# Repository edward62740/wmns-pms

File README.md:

# Particulate Matter Sensor

This sensor measures particulate matter in the air, shows readings on a display and posts the data to InfluxDB. Extention of [WMNS](https://github.com/edward62740/Wireless-Mesh-Network-System).

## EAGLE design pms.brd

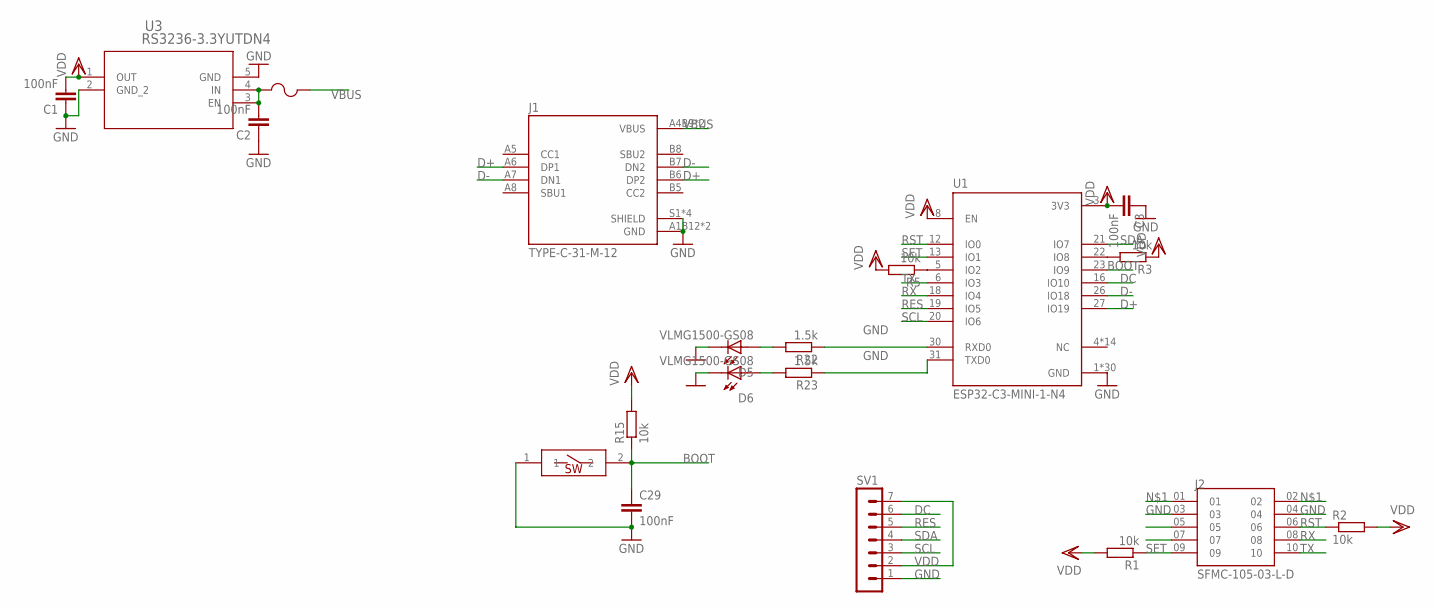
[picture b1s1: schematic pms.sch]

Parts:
C1, C2, C3, C29: 100nF; C0402
D5, D6: VLMG1500-GS08; LEDC1005X35N
F2: 1210L050YR1210LSERIES_LTF-L; 1210LSERIES_LTF-L
J1: TYPE-C-31-M-12; HRO_TYPE-C-31-M-12
J2: SFMC-105-03-L-D; SAMTEC_SFMC-105-03-L-D
R1, R2, R3, R5, R15: 10k; R0402
R22, R23: 1.5k; R0402
RESET: SMDSWITCH; RESC4217X170
SV1: MA07-1
U1: ESP32-C3-MINI-1-N4; XCVR_ESP32-C3-MINI-1-N4
U3: RS3236-3.3YUTDN4; UTDFN-1X1-4_JRT

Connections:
BOOT: C29.1, R15.1, RESET.2, U1.23 (IO9)
D+: J1.A6 (DP1), J1.B6 (DP2), U1.27 (IO19)
D-: J1.A7 (DN1), J1.B7 (DN2), U1.26 (IO18)
DC: SV1.6, U1.16 (IO10)
GND: C1.1, C2.1, C3.1, C29.2, D5.2, D6.2, J1.A1B12 (GND), J1.B1A12 (GND), J1.S1 (SHIELD), J1.S2 (SHIELD), J1.S3 (SHIELD), J1.S4 (SHIELD), J2.03, J2.04, RESET.1, SV1.1, U1.1 (GND), U1.2 (GND), U1.11 (GND), U1.14 (GND), U1.36 (GND), U1.37 (GND), U1.38 (GND), U1.39 (GND), U1.40 (GND), U1.41 (GND), U1.42 (GND), U1.43 (GND), U1.44 (GND), U1.45 (GND), U1.46 (GND), U1.47 (GND), U1.48 (GND), U1.49_1 (GND), U1.49_2 (GND), U1.49_3 (GND), U1.49_4 (GND), U1.49_5 (GND), U1.49_6 (GND), U1.49_7 (GND), U1.49_8 (GND), U1.49_9 (GND), U1.50 (GND), U1.51 (GND), U1.52 (GND), U1.53 (GND), U3.2 (GND_2), U3.5 (GND)
unnamed: C2.2, F2.2, J2.01, J2.02, U3.3 (EN), U3.4 (IN)
unnamed: R3.2, U1.22 (IO8)
unnamed: R5.1, U1.5 (IO2)
unnamed: R23.1, U1.31 (TXD0)
unnamed: R22.1, U1.30 (RXD0)
unnamed: D5.1, R22.2
unnamed: D6.1, R23.2
RES: SV1.5, U1.19 (IO5)
RST: J2.06, R2.1, U1.12 (IO0)
RX: J2.08, U1.18 (IO4)
SCL: SV1.3, U1.20 (IO6)
SDA: SV1.4, U1.21 (IO7)
SET: J2.09, R1.1, U1.13 (IO1)
TX: J2.10, U1.6 (IO3)
VBUS: F2.1, J1.A4B9 (VBUS), J1.B4A9 (VBUS)
VDD: C1.2, C3.2, R1.2, R2.2, R3.1, R5.2, R15.2, SV1.2, SV1.7, U1.3 (3V3), U1.8 (EN), U3.1 (OUT)

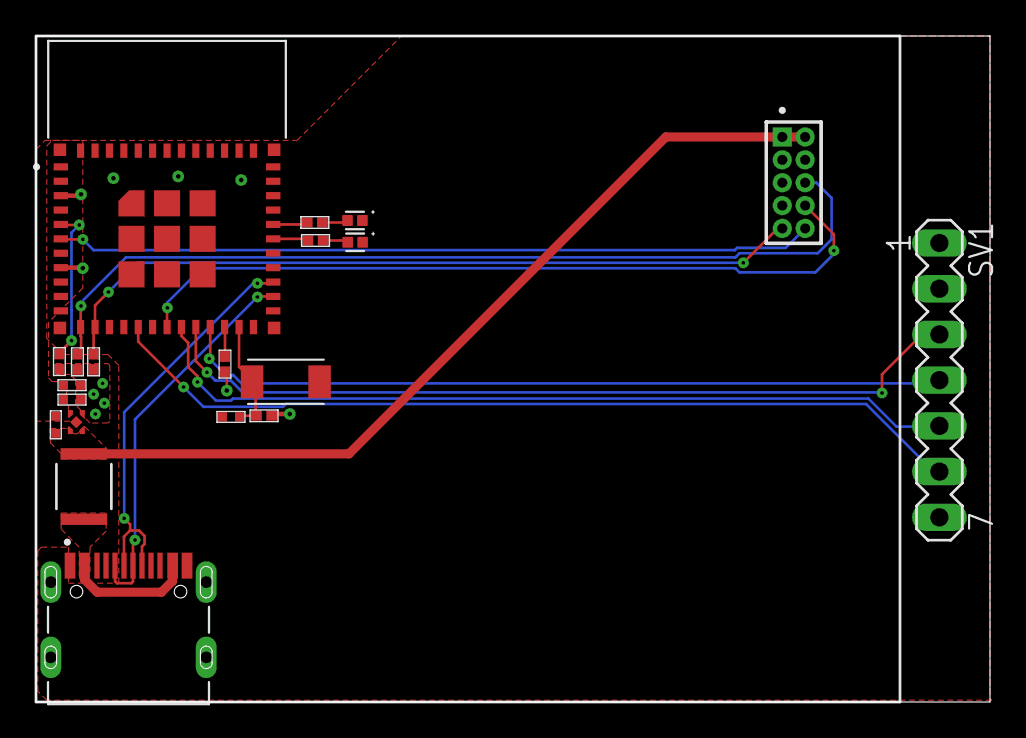
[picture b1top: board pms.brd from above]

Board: 4 copper layers, 53.0 x 37.0 mm, 20 parts (0 on the bottom side), 21 nets.

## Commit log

2022-04-08 Added PCB
2022-05-11 init

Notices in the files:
parts and their libraries:
COPYRIGHT: Copyright (C) 2022 Ultra Librarian. All rights reserved.
